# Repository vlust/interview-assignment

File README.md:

# Interview Assignment

The hardest part of this project was making design decisions. If the goal were simply to solve the scenario described in the assignment introduction, a basic multimeter would have sufficed. So with little to no design, monetary, or other constraints, I decided to base my choices on how interesting I found the solutions, of course only when there was no clear direction provided in the task.

## Task 1

The 4–20 mA interface was not specified, so I assumed a sensor with an integrated transmitter and chose a 100 Ω shunt resistor, expecting a 0.4 V to 2 V voltage output (if the transmitter in the sensor could not provide a 2V voltage for example the shunt resistor would have to be changed). If the sensor were just a passive component, a transmitter circuit would be required.

I attempted to build the circuit using components I had available to make the process more interesting. The result is this schematic: [CurrentSensorUSB\_prototype.pdf](hardware/CurrentSensorUSB_prototype/CurrentSensorUSB_prototype.pdf). I didn’t have any components to achieve galvanic isolation between the MCU and the current measurement, but I was able to use the circuit to test the Python data acquisition software. I wrote the firmware in Rust because I had never tried embedded Rust before [README.md](firmware/README.md).

The prototype circuit didn’t fully meet the requirements outlined in the task, so I created another schematic: [CurrentSensorUSB.pdf](hardware/CurrentSensorUSB/CurrentSensorUSB.pdf), along with a BOM: [CurrentSensorUSB.csv](hardware/CurrentSensorUSB/CurrentSensorUSB.csv). A more detailed explanation of the component choices can be found here: [README.md](hardware/CurrentSensorUSB/README.md). I couldn’t write the firmware for this circuit because I didn’t have the hardware or toolchain to test it.

## Task 2

The `software` folder contains a Python project with a CLI tool that can acquire a data stream over serial and generate a report based on the acquired data. An example report generated using the prototype board can be found here: [report.pdf](software/data/report_20250518_223138.pdf). More information on this task can be found in the README in the software directory: [README.md](software/README.md).

## Task 3

### 1. Procurement and Documentation

* **Bill of Materials (BOM):**

  * List each component’s reference designator, manufacturer part number, quantity, package, and tolerance. ([BOM](hardware/CurrentSensorUSB/CurrentSensorUSB.csv))

* **Supplier Selection:**

  * Order from authorized distributors (e.g., Digi‑Key, Mouser).
  * Verify lead times (aim for < 8 weeks) and minimum reel‑quantities match production volume.

* **Files for Suppliers:**

  * **PCB Fabricator:** Gerber RS‑274X package (copper, mask, silkscreen, drill), board outline (DXF/PDF), impedance spec (90 Ω differential for USB lanes).
  * **Assembly House:** BOM, pick‑and‑place (centroid) file, paste‑mask Gerbers, assembly drawing PDFs.

---

### 2. Manufacturing Steps

1. **PCB Fabrication (DFM Review)**

   * Ensure trace/space, via sizes, and 2.5 mm isolation clearance meet standards.
   * Four‑layer stack‑up (2 signal, 2 power/ground) for stable analog and controlled‑impedance USB. (Optional: separate isolation layers, though I didn’t have time to finish that layout, and it wasn’t required in the task description.)

2. **Assembly (PCBA)**

   * Provide a laser‑cut stencil for solder paste.
   * Match the reflow profile to the most temperature‑sensitive IC.
   * Perform post‑reflow AOI to catch solder defects. Since no QFN parts are used, X‑ray inspection is not necessary.

3. **Firmware Provisioning**

   * Use a simple SWD/JTAG fixture and ST‑Link (or equivalent) to program each MCU with the final Rust firmware binary.
   * It may be advisable to build a small dev board with a USB bootloader and debugger for a better firmware development experience (the current design has only SWD headers).

---

### 3. Testing and Calibration

* **Incoming Inspection (IQC):**

  * Sample critical parts (shunt resistor, op‑amp, isolator) to verify values and functionality.

* **In‑Process Checks:**

  * **Bare‑Board Test:** Use flying‑probe or ICT to catch opens/shorts.
  * **Power‑Up Smoke Test:** Limit current to \~100 mA, verify no excessive draw or heating.

* **End‑of‑Line Functional Test (FCT):**

  1. **USB Enumeration:** Ensure the board appears as a CDC/Serial device; verify VID/PID and basic loopback.

  2. **Current‑Loop Accuracy:**

     * Use a 4–20 mA precision source (≤ 0.01 % accuracy) to apply five setpoints (4, 8, 12, 16, 20 mA).
     * Read back ADC counts via USB; compute offset and gain error.
     * Adapt the Python data acquisition tool to create automatic reports (see [report\_20250518\_223138.pdf](software/data/report_20250518_223138.pdf)).
     * The MCU should communicate the firmware version and serial number on startup to build that identifier into the report.

  3. **Calibration:**

     * Adjust offset (at 4 mA) and gain (at 20 mA) by programming compensation coefficients into flash. (Trim resistors could also be added to the board for calibration.)
     * Verify mid‑point (e.g., 12 mA) to confirm linearity within tolerance.

  4. **Isolation Test:**

     * Perform a hipot test between the USB side and the sensor side to confirm isolation and leakage requirements.

* **Traceability:**

  * Assign each board a serial number; record calibration data (offset/gain) and test results in a simple CSV or database, with links to the generated reports.

---

### 4. Required Equipment & Files Summary

| **Category**             | **Files/Supplies**                                           | **Equipment**                                                                                              |
| ------------------------ | ------------------------------------------------------------ | ---------------------------------------------------------------------------------------------------------- |
| **PCB Fab**              | Gerbers, drill file, board outline (DXF/PDF), impedance spec | —                                                                                                          |
| **PCB Assembly**         | BOM (incl. alternates), pick‑and‑place, paste‑mask Gerbers   | Pick‑and‑place machine, reflow oven, AOI                                                                   |
| **Firmware/Programming** | Final Rust `.bin`/`.hex`, programming script, README         | SWD/JTAG programmer (ST‑Link), PC                                                                          |
| **Functional Testing**   | Test‑fixture drawing, FCT script (Python), calibration doc   | 4–20 mA precision source (e.g., Keithley), 6½‑digit DMM, oscilloscope, USB protocol analyzer, hipot tester |

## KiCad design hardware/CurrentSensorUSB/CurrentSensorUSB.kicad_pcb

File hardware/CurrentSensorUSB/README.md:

# Design Considerations

## 1. Microcontroller (U1: ATSAMD21E18A‑A)

  * **Built‑in USB Full‑Speed interface** simplifies serial‑over‑USB implementation.
  * Proven ecosystem and popularity
  * E‑Series package (smallest) has more than enough GPIO and ADC channels for this project.

---

## 2. Precision ADC (U3: ADS1113IDGS)

  * **16‑bit resolution** yields better than 10 µA resolution over the 4–20 mA span by adjusting the PGA settings.
  * Single‑ended input with onboard reference minimizes external parts.
  * I²C interface maps cleanly to the SAMD21 peripheral.

---

## 3. Digital Isolator (U5: ADuM1250)

  * Provides **2.5 kV galvanic isolation** on I2C lines.
  * Ensures USB‑side ground is fully isolated from the analog front end.

---

## 4. DC–DC Converter (PS1: MEE1S0503SC)

  * Generates an **isolated 3.3 V rail** from USB 5 V for the sensor‑side analog domain.
  * 150 mW output rating covers the ADS1113 + op‑amps + isolator.

---

## 5. Shunt Resistor (R2: 100 Ω LVK12)

  * Converts 4–20 mA into 0.4–2.0 V (with gain stage, maps to 0.2–1.0 V for the ADS1113).
  * **0.1 % tolerance** keeps measurement error < ±1 µA.

---

## 6. Voltage Regulator (U2: MCP1703A‑3302)

  * **3.3 V LDO** for the SAMD21 from the USB 5 V rail.

---

## 7. ESD Protection (D1: PRTR5V0U2X)

  * I wanted to incoorperate an example for circuit protection but without having a clear safety bufget i decided to keep it minimal.

---

## 8. 32.768 kHz Crystal (Y1)

  * Provides a **precision RTC clock** for timestamping the serial out.
  * Matched load capacitance (6.8 pF) aligns with the SAMD21’s XOSC32K requirements.

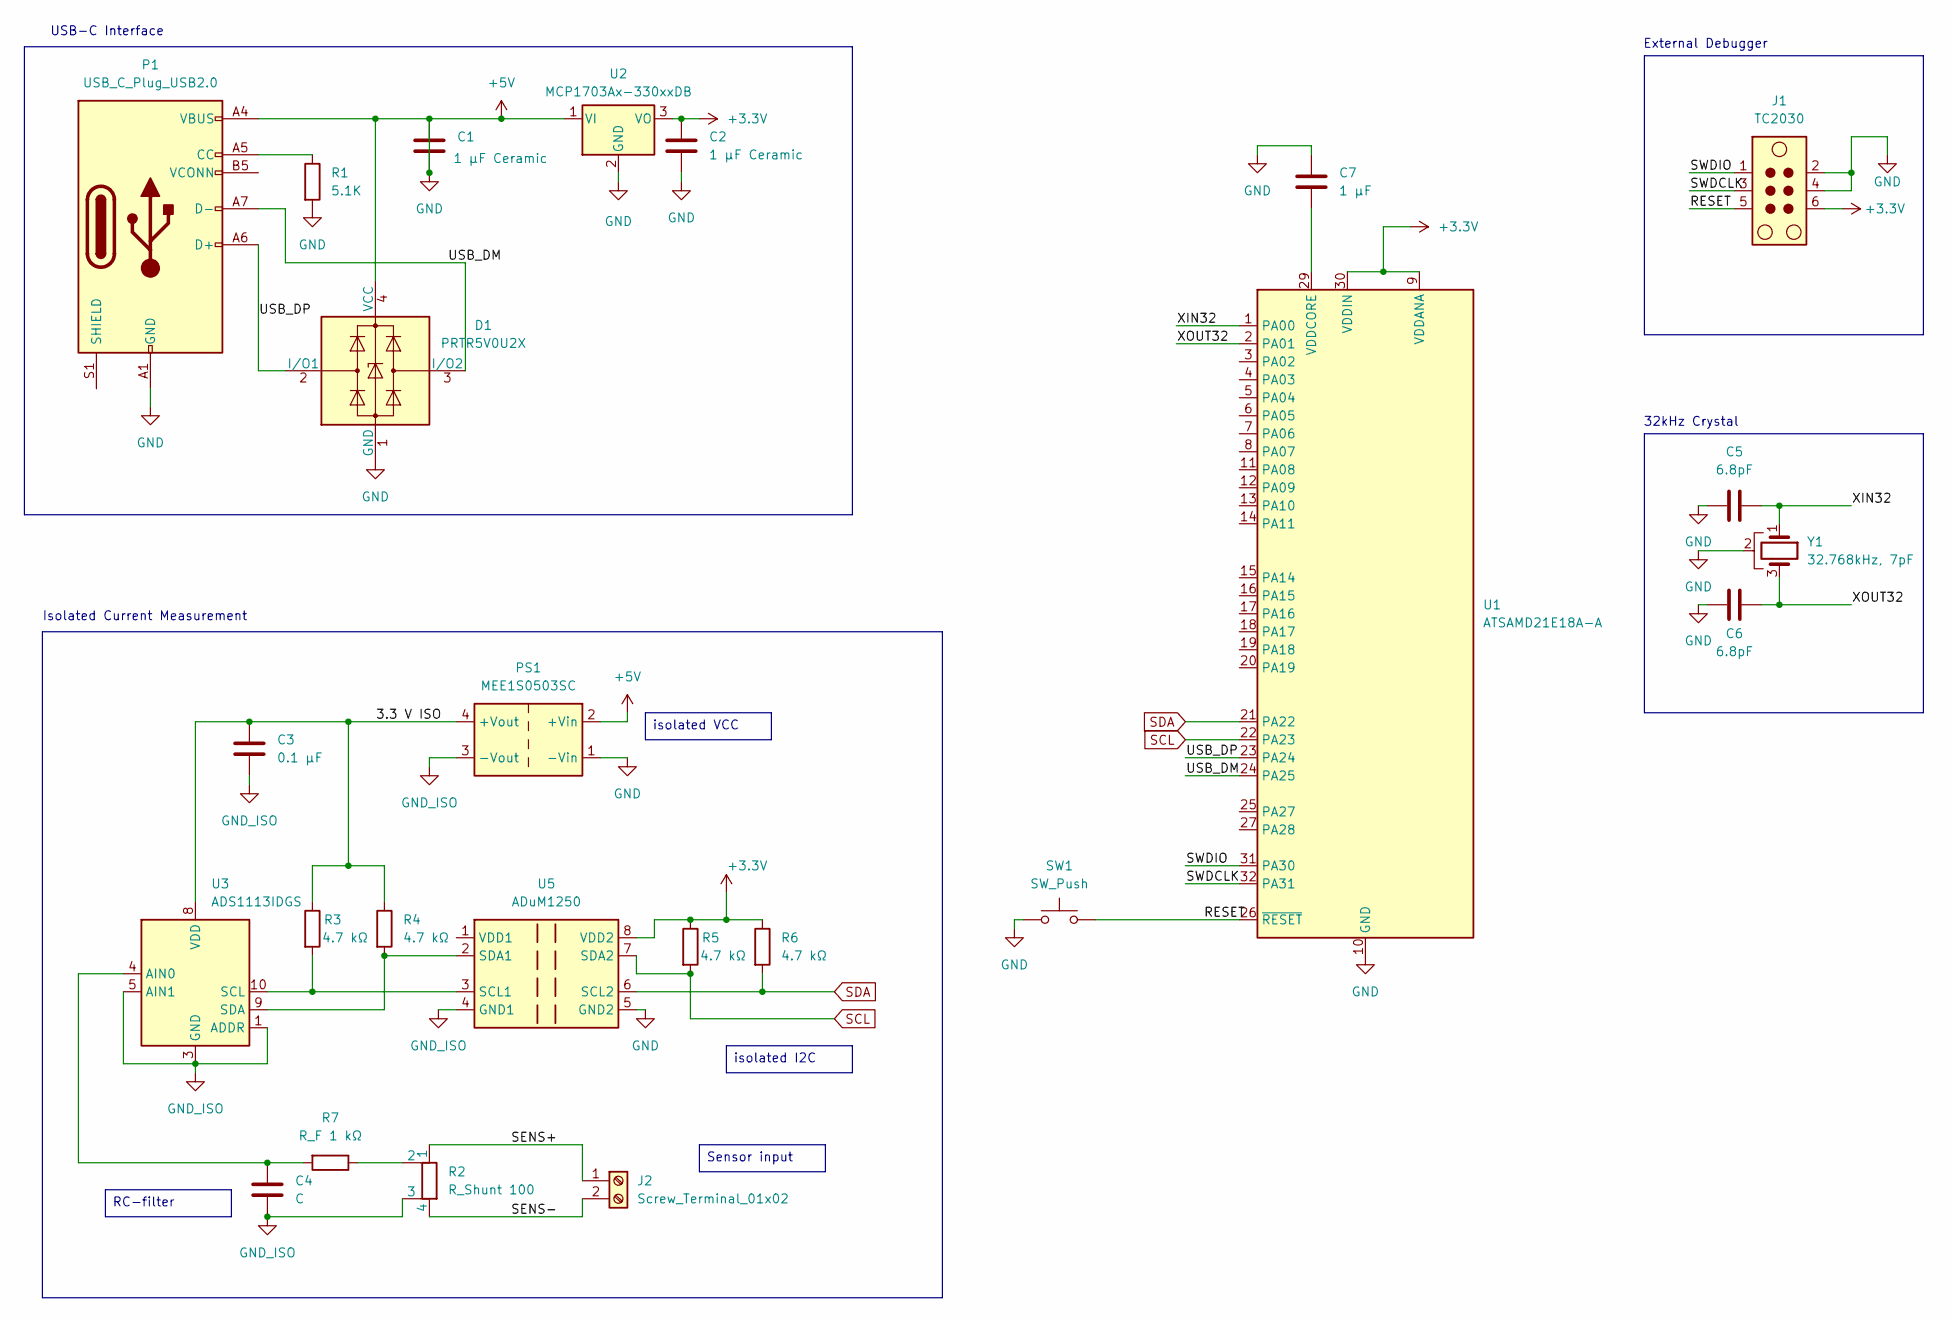
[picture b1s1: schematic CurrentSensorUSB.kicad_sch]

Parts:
C1, C2: 1 μF Ceramic; C_0603_1608Metric
C3: 0.1 μF; C_0603_1608Metric
C4: C; C_0603_1608Metric
C5, C6: 6.8pF; C_0603_1608Metric
C7: 1 μF; C_0603_1608Metric
D1: PRTR5V0U2X; SOT-143
J1: TC2030; Tag-Connect_TC2030-IDC-NL_2x03_P1.27mm_Vertical
J2: Screw_Terminal_01x02; TerminalBlock_Phoenix_MKDS-1,5-2_1x02_P5.00mm_Horizontal
P1: USB_C_Plug_USB2.0; USB_C_Plug_Molex_105444
PS1: MEE1S0503SC; Converter_DCDC_Murata_MEE1SxxxxSC_THT
R1: 5.1K; R_0603_1608Metric
R2: R_Shunt 100; R_Shunt_Ohmite_LVK12
R3, R4, R5, R6: 4.7 kΩ; R_0603_1608Metric
R7: R_F 1 kΩ; R_0603_1608Metric
SW1: SW_Push; SW_MEC_5GSH9
U1: ATSAMD21E18A-A; TQFP-32_7x7mm_P0.8mm
U2: MCP1703Ax-330xxDB; SOT-223-3_TabPin2
U3: ADS1113IDGS; TSSOP-10_3x3mm_P0.5mm
U5: ADuM1250; SOIC-8_3.9x4.9mm_P1.27mm
Y1: 32.768kHz, 7pF; Crystal_SMD_0603-4Pin_6.0x3.5mm

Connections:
+3.3V: C2.1, J1.6, R5.1, R6.1, U1.9 (VDDANA), U1.30 (VDDIN), U2.3 (VO), U5.8 (VDD2)
+5V: C1.1, C1.2, C2.2, C5.2, C6.2, C7.1, D1.1 (GND), D1.4 (VCC), J1.2, J1.4, P1.A1 (GND), P1.A4 (VBUS), P1.A9 (VBUS), P1.A12 (GND), P1.B1 (GND), P1.B4 (VBUS), P1.B9 (VBUS), P1.B12 (GND), PS1.1 (-Vin), PS1.2 (+Vin), R1.2, SW1.1, U1.10 (GND), U1.28 (GND), U2.1 (VI), U2.2 (GND), U5.5 (GND2), Y1.2
/3.3 V ISO: C3.1, PS1.4 (+Vout), R3.1, R4.1, U3.8 (VDD)
/RESET: J1.5, SW1.2, U1.26 (~RESET)
/SENS+: J2.1, R2.1
/SENS-: J2.2, R2.4
/SWDCLK: J1.3, U1.32 (PA31)
/SWDIO: J1.1, U1.31 (PA30)
/USB_DM: D1.3 (I/O2), P1.A7 (D-), U1.24 (PA25)
/USB_DP: D1.2 (I/O1), P1.A6 (D+), U1.23 (PA24)
/XIN32: C5.1, U1.1 (PA00), Y1.1
/XOUT32: C6.1, U1.2 (PA01), Y1.3
GND_ISO: C3.2, C4.2, PS1.3 (-Vout), R2.3, U3.1 (ADDR), U3.3 (GND), U3.5 (AIN1), U5.4 (GND1)
unnamed: P1.A5 (CC), R1.1
unnamed: R2.2, R7.1
unnamed: C7.2, U1.29 (VDDCORE)
unnamed: C4.1, R7.2, U3.4 (AIN0)
unnamed: R3.2, U3.10 (SCL), U5.3 (SCL1)
unnamed: R4.2, U3.9 (SDA), U5.2 (SDA1)
SCL: R5.2, U1.22 (PA23), U5.7 (SDA2)
SDA: R6.2, U1.21 (PA22), U5.6 (SCL2)

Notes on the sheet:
32kHz Crystal
USB-C Interface
Isolated Current Measurement
External Debugger
isolated VCC
isolated I2C
Sensor input
RC-filter

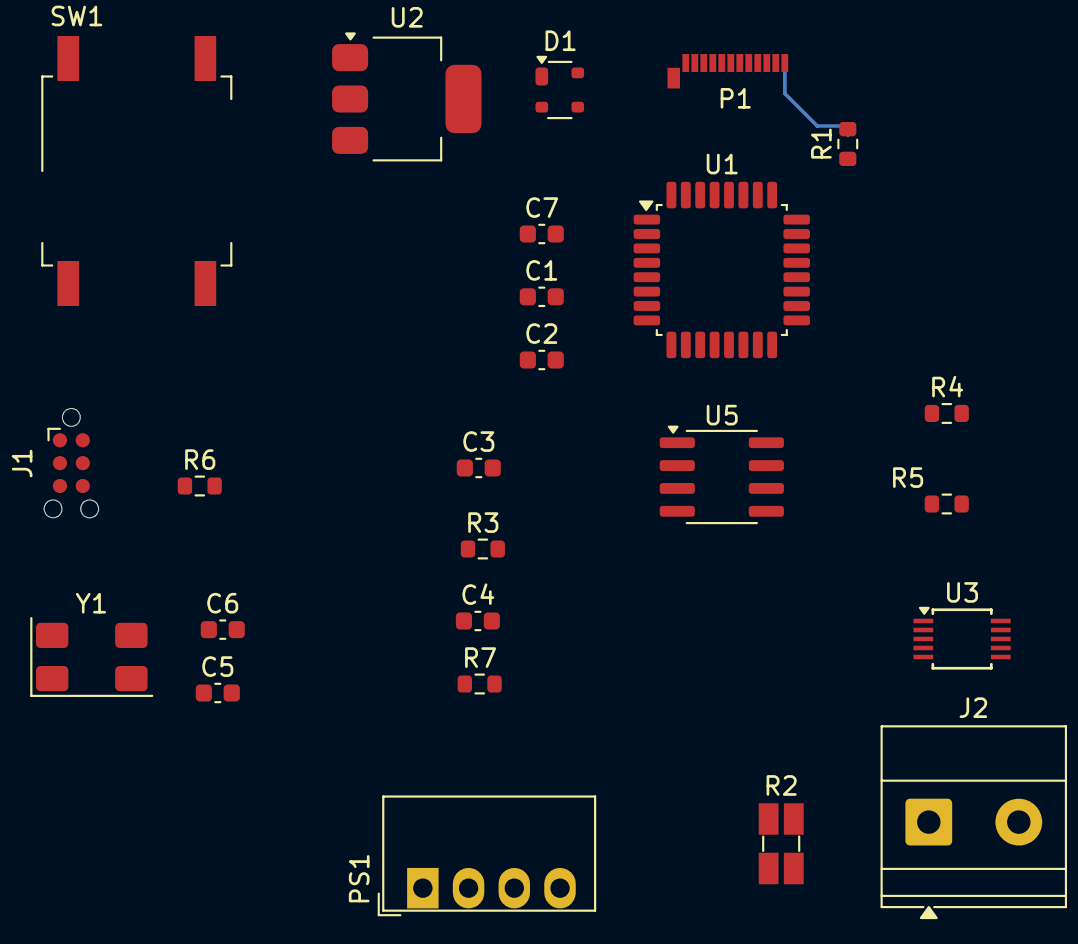
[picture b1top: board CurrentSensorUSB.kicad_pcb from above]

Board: 2 copper layers, 25 parts (0 on the bottom side), 21 nets.

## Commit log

2025-05-18 init
2025-05-18 added prototype schematics
2025-05-18 add .zip to gitignore for backup files
2025-05-18 added schematics for final version
2025-05-18 not saved
2025-05-18 ... cant type gitignore
2025-05-18 initilized uv python project
2025-05-18 working emulation on //loop
2025-05-18 Add .python-version file and update plot_data.py for configurable duration
2025-05-18 rename data acquisition and plotting from serial input
2025-05-18 Refactor emulator functionality into a separate module and update main script to use it
2025-05-18 Add report generation functionality with LaTeX template for data acquisition
2025-05-18 Enhance data acquisition script to save plots and reports with timestamped filenames
2025-05-18 project restructure
2025-05-18 cleanup
2025-05-18 readme edits
2025-05-18 because of uv python not needed as dependency
2025-05-18 check for pdflatex instllations
2025-05-18 changes in schematic
2025-05-18 added example output
2025-05-18 example csv
2025-05-18 bom edited
2025-05-18 aded runst firmware for prototype circuit
2025-05-18 pdf schematics
2025-05-18 simplify firmware serial out
2025-05-18 added docs for task 1 and 2
2025-05-18 simplify sw readme example
2025-05-18 spelling
2025-05-18 pcb layout attempt
2025-05-18 i dont even know what i changed here
2025-05-18 added task 3 docs
2025-05-18 moved report template to correct position
2025-05-18 improved spelling in readme
2025-05-18 vscode ignore
2025-05-18 fixed file link
2025-05-18 added readme for hardware considerations
2025-05-18 small changes in the schematics pdf
2025-05-18 added link to firmware readme
2025-05-18 doc changes
2025-05-18 forgot to save schmatic
2025-05-18 software project refactor
2025-05-19 headline
2025-05-19 some small post release changes, that i forgot/kept bugging me. official release is tagged
